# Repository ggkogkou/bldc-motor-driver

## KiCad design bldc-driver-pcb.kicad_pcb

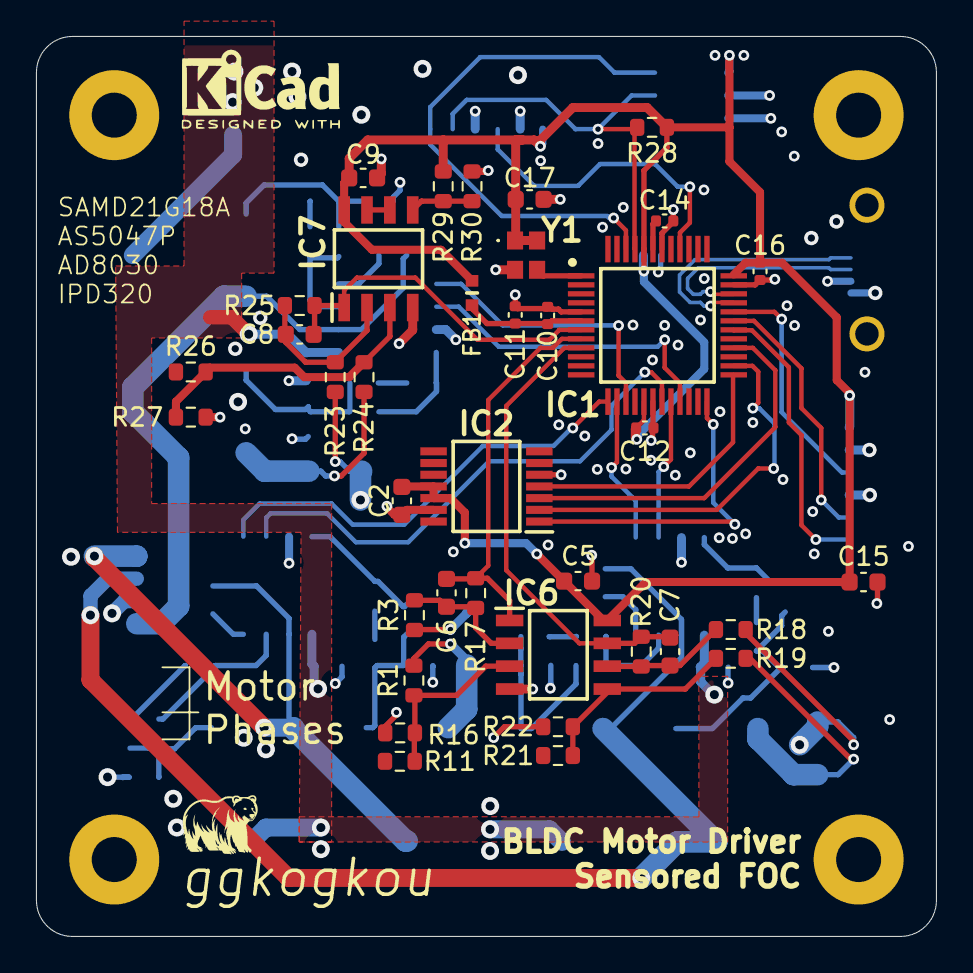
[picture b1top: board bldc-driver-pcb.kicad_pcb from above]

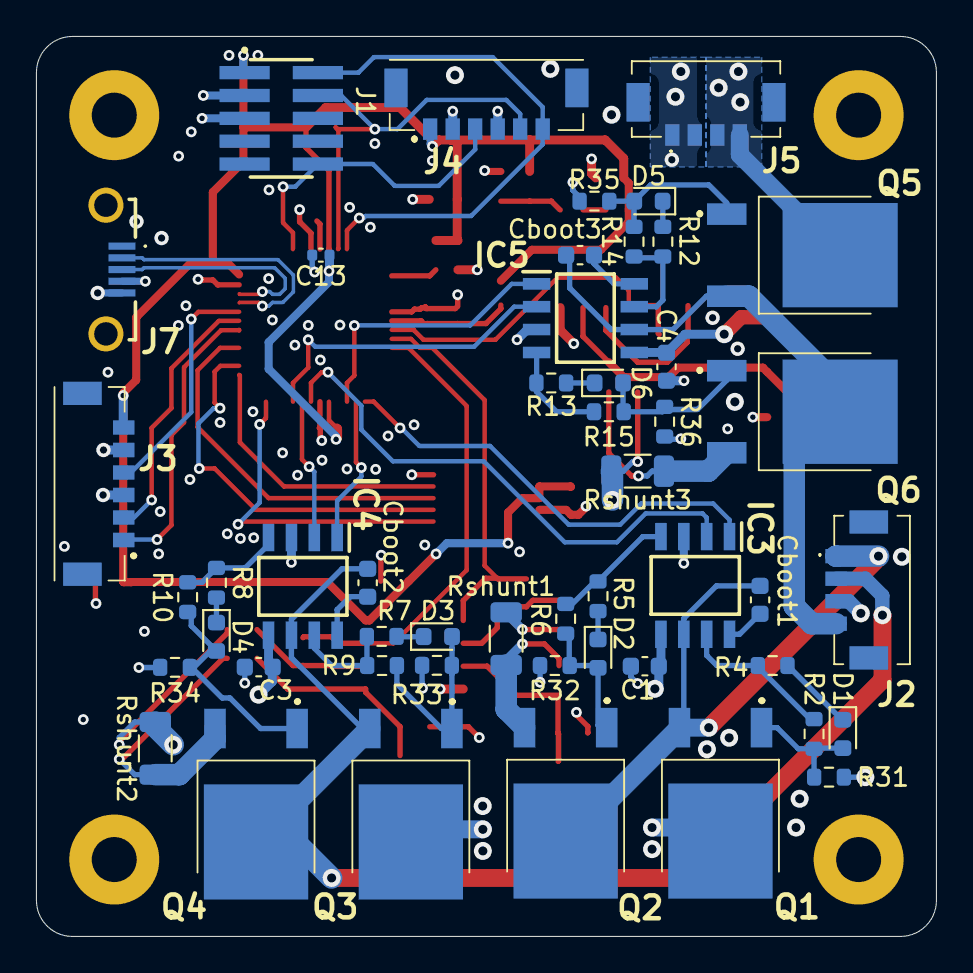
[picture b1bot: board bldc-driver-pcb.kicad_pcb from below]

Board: 4 copper layers, 50.0 x 50.0 mm, 86 parts (49 on the bottom side), 62 nets.

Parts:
C1, C3, C4: C_Small; C_0603_1608Metric
C2, C5, C9, C17: 0.1u; C_0603_1608Metric
C6, C7, C8: TBD; C_0603_1608Metric
C10, C12, C13, C16: 0.1u; C_0402_1005Metric
C11: 10u; C_0402_1005Metric
C14: 1u; C_0402_1005Metric
C15: 10u; C_0603_1608Metric
Cboot1, Cboot2, Cboot3: TBD; C_0603_1608Metric
D1, D2, D3, D4, D5, D6: D_0603_1608Metric
FB1: FerriteBead; BLM18SP221SN1B
IC1: ATSAMD21G18A-AFT; ATSAMD21G18A-QFP
IC2: AS5047P-ATSM; AS5047P
IC3, IC4, IC5: L6498D
IC6, IC7: AD8030ARZ; AD8030
J1: FTSH-105-XX-X-DV; SAMTEC_FTSH-105-XX-X-DV
J2, J5: 505567-0471; 5055670471
J3, J4: 505567-0671; 5055670671
J7: USB3140-30-0170-1-C; USB31403001700C
Q1, Q2, Q3, Q4, Q5, Q6: IPD320N20N3GATMA1; BTS3035TFATMA1
R1, R3, R11, R16, R17, R18, R19, R20, R21, R22, R23, R24, R25, R26, R27, R29, R30, R31, R32, R33, R34, R35, R36: 10k; R_0603_1608Metric
R2, R4, R5, R6, R7, R8, R9, R10, R12, R13, R14, R15: TBD; R_0603_1608Metric
R28: 1k; R_0603_1608Metric
Rshunt1, Rshunt2, Rshunt3: 100m; R_1206_3216Metric
Y1: LFSPXO009686

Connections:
+3V3: C2.1, C5.2, C9.2, C12.1, C13.1, C15.1, C16.1, C17.2, FB1.1, IC1.17 (VDDIO_1), IC1.36 (VDDIO_2), IC1.44 (VDDIN), IC2.11 (VDD), IC2.12 (VDD3V), IC6.8 (+VS), IC7.8 (+VS), J1.01, J3.6, J4.1, R28.1, R29.1, Y1.1 (TRI-STATE_OPERATION), Y1.4 (+VS)
/Current Sensing/CSA_1_IN+: Q2.3 (S), R1.2, Rshunt1.1
/Current Sensing/CSA_1_VOUT: C6.2, IC1.8 (PB09), IC6.1 (VOUT1), R17.2
/Current Sensing/CSA_2_IN+: Q4.3 (S), R19.1, Rshunt2.1
/Current Sensing/CSA_2_VOUT: C7.1, IC1.9 (PA04), IC6.7 (+VOUT_2), R20.1
/Current Sensing/CSA_3_IN+: Q6.3 (S), R24.2, Rshunt3.1
/Current Sensing/CSA_3_VOUT: C8.2, IC1.7 (PB08), IC7.1 (VOUT1), R25.2
/Microcontroller/ENCODER_CSn: IC1.24 (PA15), IC2.1 (CSN)
/Microcontroller/SERCOM1_PAD0: IC1.25 (PA16), IC2.4 (MOSI)
/Microcontroller/SERCOM1_PAD1: IC1.26 (PA17), IC2.2 (CLK)
/Microcontroller/SERCOM1_PAD3: IC1.28 (PA19), IC2.3 (MISO)
/Microcontroller/TCC0_WO0: IC1.13 (PA08), IC3.1 (HIN)
/Microcontroller/TCC0_WO1: IC1.14 (PA09), IC4.1 (HIN)
/Microcontroller/TCC0_WO2: IC1.15 (PA10), IC5.1 (HIN)
/Microcontroller/TCC0_WO4: IC1.19 (PB10), IC3.2 (LIN)
/Microcontroller/TCC0_WO5: IC1.20 (PB11), IC4.2 (LIN)
/Microcontroller/TCC0_WO6: IC1.21 (PA12), IC5.2 (LIN)
/Microcontroller/USB_D+: IC1.34 (PA25), J7.3 (D+)
/Microcontroller/USB_D-: IC1.33 (PA24), J7.2 (D-)
/Microcontroller/VDDANA: C10.1, C11.1, FB1.2, IC1.6 (VDDANA)
/Microcontroller/VDDCORE: C14.1, IC1.43 (VDDCORE)
/Microcontroller/XIN32: IC1.1 (PA00), Y1.3 (OUTPUT)
/SWCLK: IC1.45 (PA30), J1.04, J4.5, R28.2
/SWDIO: IC1.46 (PA31), J1.02, J4.6
/Three-Phase Inverter/HALF_BRIDGE_1_OUT: Cboot1.2, IC3.6 (OUT), J2.1, Q1.3 (S), Q2.2 (D)
/Three-Phase Inverter/HALF_BRIDGE_2_OUT: Cboot2.2, IC4.6 (OUT), J2.2, Q3.3 (S), Q4.2 (D)
/Three-Phase Inverter/HALF_BRIDGE_3_OUT: Cboot3.2, IC5.6 (OUT), J2.4, Q5.3 (S), Q6.2 (D)
/USART3_Rx: IC1.31 (PA22), J3.2
/USART3_Tx: IC1.32 (PA23), J3.4
/USART5_Tx: IC1.30 (PA21), J3.1
/nRST: IC1.40 (~RESET), J1.10, J4.3
GND: C1.1, C2.2, C3.1, C4.1, C5.1, C9.1, C10.2, C11.2, C12.2, C13.2, C14.2, C15.2, C16.2, C17.1, IC1.5 (GNDANA), IC1.18 (GND_1), IC1.35 (GND_2), IC1.42 (GND_3), IC2.5 (TEST), IC2.13 (GND), IC3.3 (GND), IC4.3 (GND), IC5.3 (GND), IC6.4 (-VS), IC7.4 (-VS), J1.03, J1.05, J2.3, J3.3, J3.5, J4.2, J4.4, J5.1, J5.2, J7.4 (ID), J7.5 (GND), J7.MH2, R3.1, R16.2, R18.2, R22.1, R23.1, R27.2, R30.2, R31.2, R32.2, R33.2, R34.2, R35.2, R36.2, Rshunt1.2, Rshunt2.2, Rshunt3.2, Y1.2 (GND)
unnamed: D1.2 (A), Q1.1 (G), R2.2, R31.1
unnamed: D1.1 (K), R4.2
unnamed: D2.2 (A), Q2.1 (G), R6.2, R32.1
unnamed: D2.1 (K), R5.2
unnamed: D3.2 (A), Q3.1 (G), R9.2, R33.1
unnamed: D3.1 (K), R7.2
unnamed: D4.2 (A), Q4.1 (G), R10.2, R34.1
unnamed: D4.1 (K), R8.2
unnamed: D5.2 (A), Q5.1 (G), R14.2, R35.1
unnamed: D5.1 (K), R12.2
unnamed: D6.2 (A), Q6.1 (G), R15.2, R36.1
unnamed: D6.1 (K), R13.2
unnamed: Cboot1.1, IC3.8 (BOOT)
unnamed: IC3.7 (HVG), R2.1, R4.1
unnamed: IC3.4 (LVG), R5.1, R6.1
unnamed: Cboot2.1, IC4.8 (BOOT)
unnamed: IC4.7 (HVG), R7.1, R9.1
unnamed: IC4.4 (LVG), R8.1, R10.1
unnamed: Cboot3.1, IC5.8 (BOOT)
unnamed: IC5.7 (HVG), R12.1, R14.1
unnamed: IC5.4 (LVG), R13.1, R15.1
unnamed: IC6.3 (+IN_1), R1.1, R11.2, R16.1
unnamed: IC6.5 (+IN_2), R19.2, R21.1, R22.2
unnamed: C6.1, IC6.2 (-IN_1), R3.2, R17.1
unnamed: C7.2, IC6.6 (-IN_2), R18.1, R20.2
unnamed: IC7.3 (+IN_1), R24.1, R26.2, R27.1
unnamed: IC7.5 (+IN_2), R29.2, R30.1
unnamed: IC7.6 (-IN_2), IC7.7 (+VOUT_2)
unnamed: C8.1, IC7.2 (-IN_1), R23.2, R25.1
VBUS: C1.2, C3.2, C4.2, IC3.5 (VCC), IC4.5 (VCC), IC5.5 (VCC), J5.3, J5.4, Q1.2 (D), Q3.2 (D), Q5.2 (D)

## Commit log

2025-12-04 Add MCU stuff, cortex debug connector and docs
2025-12-04 Connect unused op amp channel
2025-12-04 Add gitignore
2025-12-04 Clear git cache
2025-12-05 Initial routing
2025-12-05 Minor changes
2025-12-08 More routing
2025-12-11 Reroute everything
2025-12-12 Finalize layout -- VREF pending
2025-12-12 Add connector for motor phases
2025-12-12 Fix DRC violations
2025-12-12 Add some silkscreen
2025-12-28 Relocate VM & phase connectors
2025-12-28 Add 32.768kHz external clock & specify ferrite bead part number
2025-12-28 Vmotor power plane
2026-01-25 Layout QOL changes
